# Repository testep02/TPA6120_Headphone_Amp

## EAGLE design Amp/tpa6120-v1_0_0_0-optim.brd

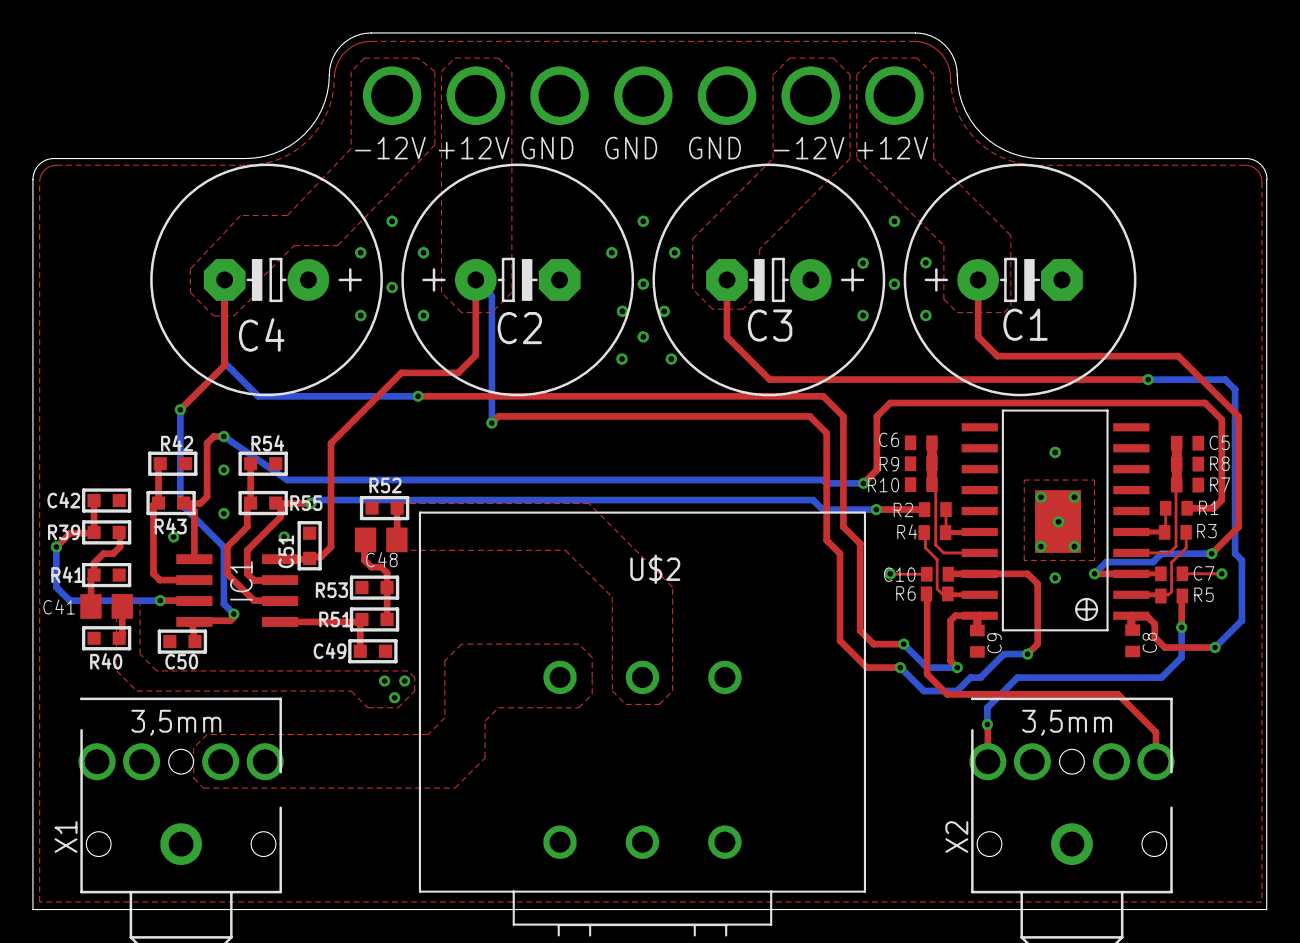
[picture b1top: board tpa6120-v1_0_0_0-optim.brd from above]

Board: 2 copper layers, 74.9 x 53.2 mm, 41 parts (0 on the bottom side), 25 nets.

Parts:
C1, C2, C3, C4: 470uF; E5-13
C5, C6, C7, C8, C9, C10: 100nF/100V; C0402
C41, C48: 100nF/50V; C0805
C42, C49: 100pF/100V; C0603
C50, C51: 100nF/50V; C0603
IC1: AD8620R; SO8
R1, R2, R3, R4, R7, R8, R9, R10: 1k0; R0402
R5, R6: 10; R0402
R39, R42, R43, R51, R54, R55: 1k0; R0603
R40, R41, R52, R53: 470k; R0603
U$1: TPA6120_TPA6120
U$2: ALPS_RK27
X1, X2: STEREOJACK; STX3100

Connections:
+12V_L: C1.+, C7.1, U$1.3
+12V_R: C2.+, C10.1, C51.1, IC1.8, U$1.18
-12V_L: C3.-, C8.1, U$1.1
-12V_R: C4.-, C9.1, C50.1, IC1.4, U$1.20
BUFF_L_OUT: IC1.1, R1.2, R43.1
BUFF_R_OUT: IC1.7, R2.2, R55.1
GND: C1.-, C2.-, C3.+, C4.+, C5.2, C6.2, C7.2, C8.2, C9.2, C10.2, C42.2, C49.2, C50.2, C51.2, R7.2, R8.2, R9.2, R10.2, R40.2, R41.2, R42.2, R52.2, R53.2, R54.2, U$1.6, U$1.7, U$1.8, U$1.9, U$1.10, U$1.11, U$1.12, U$1.13, U$1.14, U$1.15, U$1.21, U$2.I1, U$2.I2, X1.1, X2.1
HP_IN_L: U$2.G1, X1.2, X1.3
HP_IN_R: U$2.G2, X1.4, X1.5
INVERT_L: R1.1, R3.2, U$1.5
INVERT_R: R2.1, R4.2, U$1.16
unnamed: C5.1, R7.1, R8.1, U$1.4
unnamed: C6.1, R9.1, R10.1, U$1.17
unnamed: R6.1, X2.5
unnamed: R5.1, X2.2
unnamed: C41.2, R39.2, R41.1
unnamed: C42.1, IC1.3, R39.1
unnamed: IC1.2, R42.1, R43.2
unnamed: C48.2, R51.2, R53.1
unnamed: C49.1, IC1.5, R51.1
unnamed: IC1.6, R54.1, R55.2
OUT_L: R3.1, R5.2, U$1.2
OUT_R: R4.1, R6.2, U$1.19
POT_L: C41.1, R40.1, U$2.O1
POT_R: C48.1, R52.1, U$2.O2

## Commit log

2014-08-19 :lollipop: Added .gitattributes & .gitignore files
2014-08-19 Initial Checkin
    This initial checkin has the amp designed as one board. The power
    supply, amp, and buffer are all one piece.
2014-08-19 Created Modular branch
    This commit splits the power supply from the amp itself.
2014-08-19 Optimized with 2-channel op-amp
    Optimized with 2-channel op-amp

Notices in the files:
parts and their libraries:
rc-master-smd: Copyright (C) 2007, Bob Starr
